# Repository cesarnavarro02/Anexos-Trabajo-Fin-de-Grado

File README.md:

# ANEXOS

## Anexo I: Códigos fuente
Este es el anexo de códigos. En él se encuentran todos los scripts realizados durante la elaboración del TFG. A continuación, se enumeran estos programas junto con una pequeña descripción:

- **GeneradorPerfilNACA.py**: Este programa genera un archivo ".stl" en el cual se encuentra el perfil NACA cuatro dígitos del código que ha sido introducido por el usuario.
- **ProgramaPlaca.py**: Este es el programa que gobierna el funcionamiento de la RaspberryPi.
- **GeneradorBlandAltman.py**: Este programa genera un gráfico Bland-Altman de las mediciones de presión.
- **GeneradorGraficasCp.py**: Este es el programa que elabora la gráfica de coeficientes de presión.

## Anexo II: Manuales y hojas de características
Este es el anexo de Manuales y Hojas de características. Como su propio nombre indica, en él se encuentran los manuales y hojas de características de componentes y sistemas que intervienen en el trabajo:

- **Datasheet SDP8xx-Digital**: Hoja de características del sensor de presión.
- **manual-anemometro-pce-hvac-2**: Manual del manómetro digital.
- **raspberry-pi-4-datasheet**: Hoja de características de la Raspberry Pi.

## Anexo III: Planos
En este Anexo se encuentra el plano del perfil acotado con sus cotas en milímetros. El documento tiene el nombre de `DibujoAla.pdf`.

## Anexo IV: Archivos para fabricación de placas
En este Anexo se encuentran los archivos del esquemático y del footprint de las placas junto con la librería con los componentes que se han diseñado. Para utilizar estos archivos es necesario tener instalado el software Eagle en su versión 7.5. Se debe crear un nuevo proyecto donde se importarán tanto el esquemático como el footprint de la placa que se desee fabricar. Además, se debe importar la librería que contiene el nombre `CESAR.lbr`, que contiene los componentes específicos de las placas.

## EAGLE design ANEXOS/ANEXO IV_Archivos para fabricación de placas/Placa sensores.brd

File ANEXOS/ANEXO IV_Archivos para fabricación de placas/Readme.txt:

En este Anexo se encuentran los archivos del esquemático y de el footprint de las placas junto con la librería con los
componentes que se han diseñado. Para utilizar estos archivos es necesario tener instalado el software Eagle en su 
versión 7.5. Se debe crear un nuevo proyecto donde se importarán tanto el esquemático como el footprint de la placa 
que se desee fabricar. Además se debe importar la librearía que contiene con nombre CESAR.lbr, que contiene los componentes
específicos de las placas.

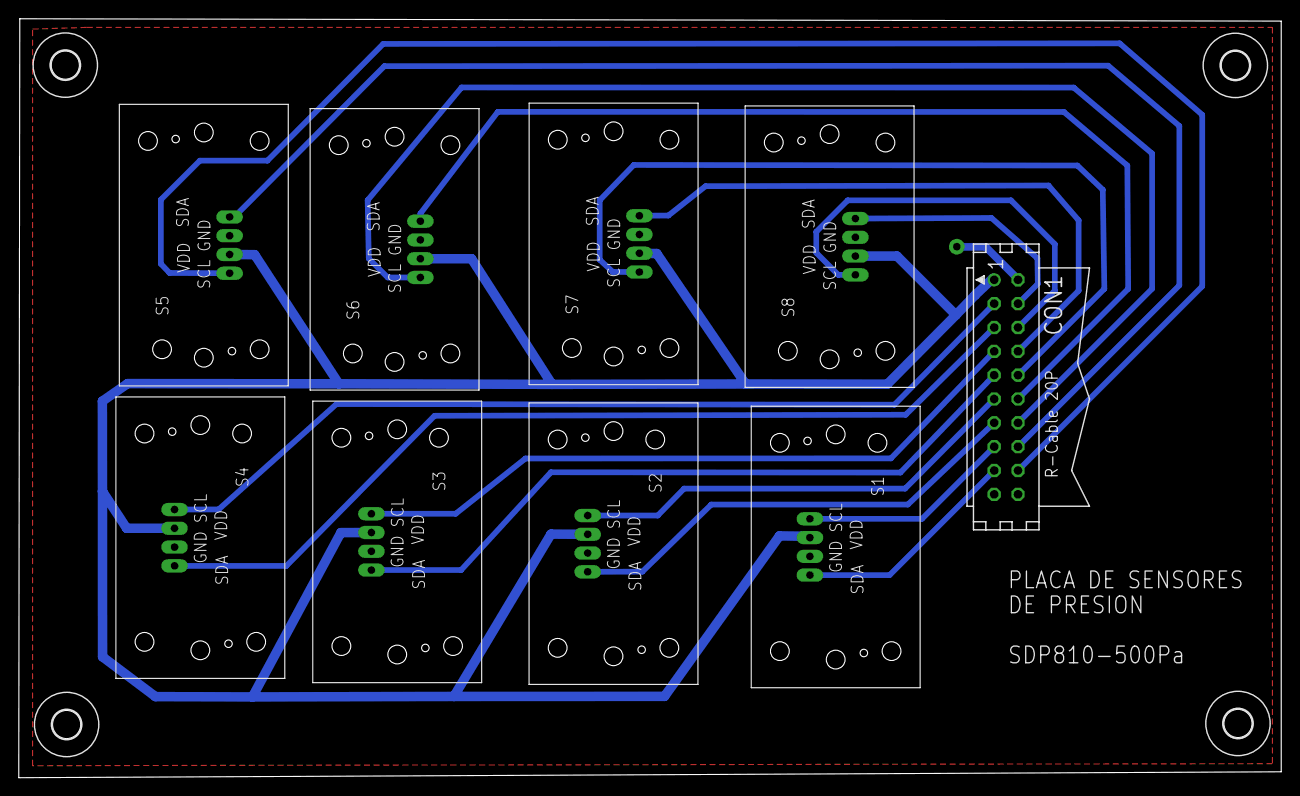
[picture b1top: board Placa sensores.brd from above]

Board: 2 copper layers, 134.5 x 80.9 mm, 13 parts (0 on the bottom side), 18 nets.

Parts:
CON1: CON20
H1, H2, H3, H4: MOUNT-HOLE3.0; 3,0
S1, S2, S3, S4, S5, S6, S7, S8: SDP810-500PA

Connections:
GND: CON1.2, S1.GND, S2.GND, S3.GND, S4.GND, S5.GND, S6.GND, S7.GND, S8.GND
unnamed: CON1.1, S1.VDD, S2.VDD, S3.VDD, S4.VDD, S5.VDD, S6.VDD, S7.VDD, S8.VDD
unnamed: CON1.6, S8.SCL
unnamed: CON1.8, S7.SDA
unnamed: CON1.10, S7.SCL
unnamed: CON1.18, S5.SCL
unnamed: CON1.16, S5.SDA
unnamed: CON1.14, S6.SCL
unnamed: CON1.4, S8.SDA
unnamed: CON1.12, S6.SDA
unnamed: CON1.3, S4.SCL
unnamed: CON1.5, S4.SDA
unnamed: CON1.7, S3.SCL
unnamed: CON1.9, S3.SDA
unnamed: CON1.17, S1.SDA
unnamed: CON1.15, S1.SCL
unnamed: CON1.11, S2.SCL
unnamed: CON1.13, S2.SDA

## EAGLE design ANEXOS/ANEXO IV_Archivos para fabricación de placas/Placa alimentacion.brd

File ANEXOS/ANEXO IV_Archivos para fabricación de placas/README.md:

En este Anexo se encuentran los archivos del esquemático y del footprint de las placas junto con la librería con los componentes que se han diseñado. Para utilizar estos archivos es necesario tener instalado el software **Eagle** en su versión 7.5. Se debe crear un nuevo proyecto donde se importarán tanto el esquemático como el footprint de la placa que se desee fabricar. Además, se debe importar la librería con el nombre **CESAR.lbr**, que contiene los componentes específicos de las placas.

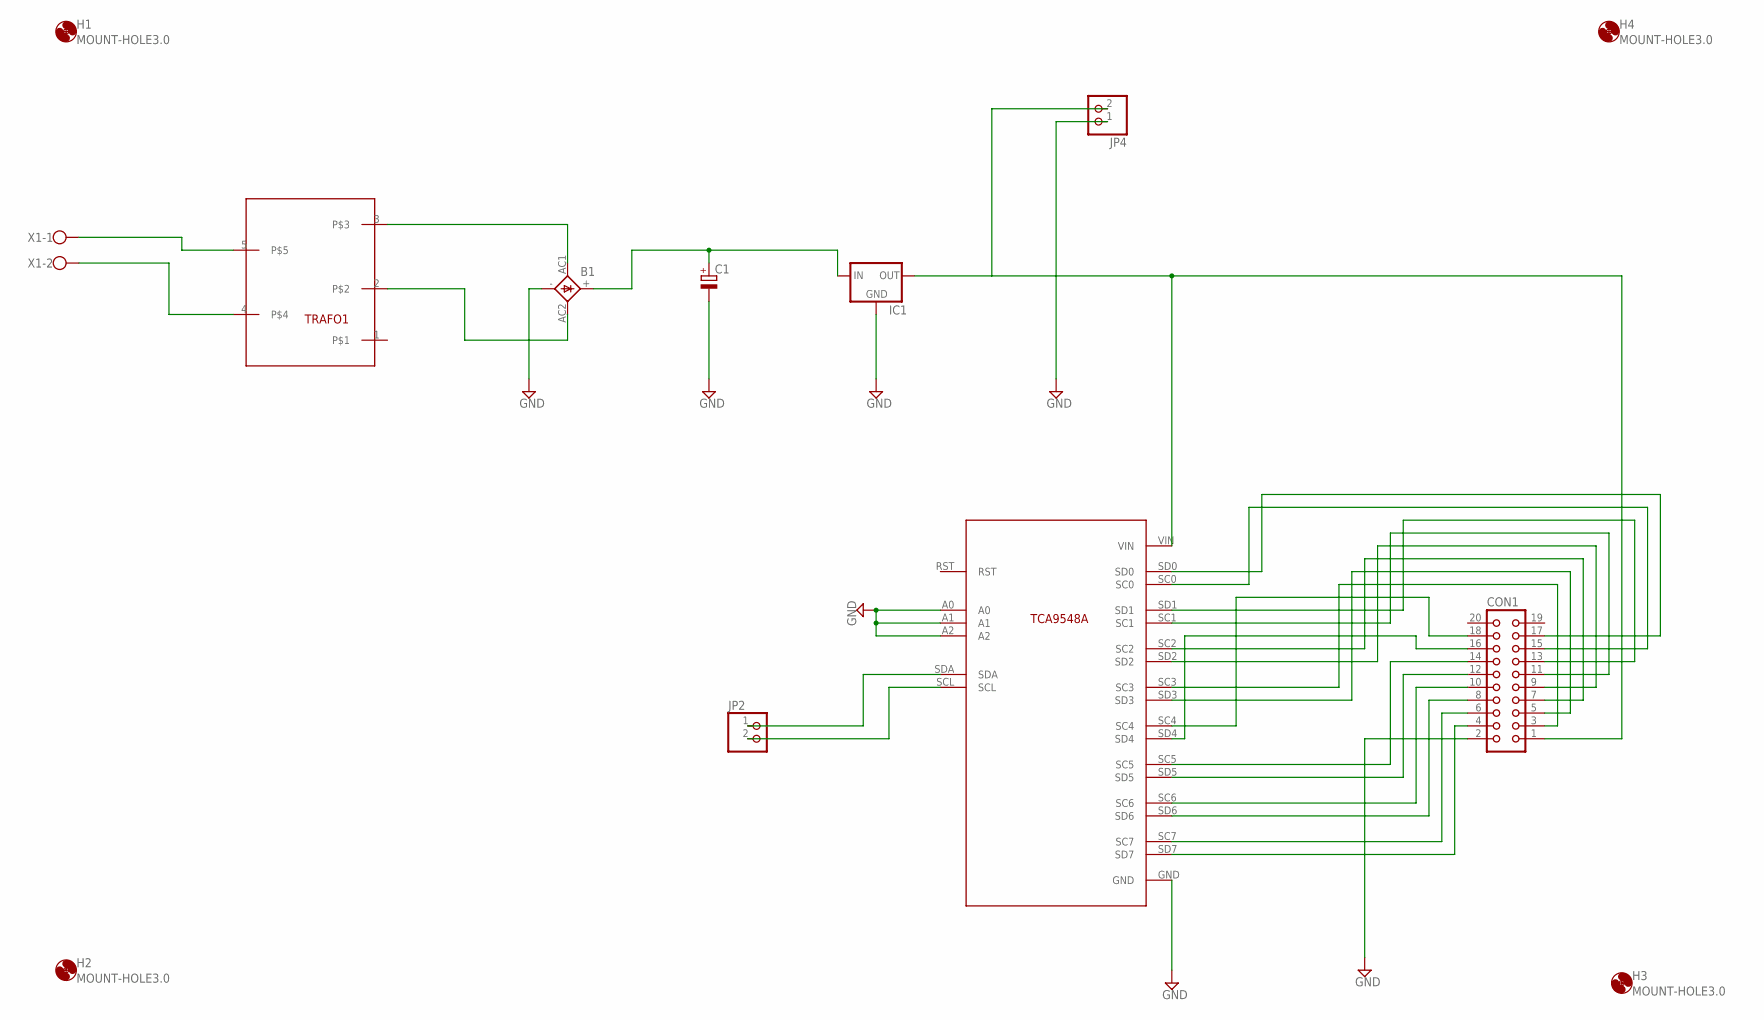
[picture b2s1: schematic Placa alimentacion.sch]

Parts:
B1: KBU
C1: CPOL-EUE5-8.5; E5-8,5
CON1: CON20
H1, H2, H3, H4: MOUNT-HOLE3.0; 3,0
IC1: 78MXXL
JP2, JP4: PINHD-1X2; 1X02
TRAFO1: ARISTON_TR5309
U$1: TCA9548A
X1: W237-102

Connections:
GND: B1.-, C1.-, CON1.2, IC1.GND, JP4.1, U$1.A0, U$1.A1, U$1.A2, U$1.GND
unnamed: TRAFO1.5, X1.1
unnamed: TRAFO1.4, X1.2
unnamed: B1.AC1, TRAFO1.3
unnamed: B1.AC2, TRAFO1.2
unnamed: B1.+, C1.+, IC1.IN
unnamed: CON1.3, U$1.SC3
unnamed: CON1.5, U$1.SD3
unnamed: CON1.7, U$1.SC2
unnamed: CON1.9, U$1.SD2
unnamed: CON1.11, U$1.SC1
unnamed: CON1.13, U$1.SD1
unnamed: CON1.15, U$1.SC0
unnamed: CON1.17, U$1.SD0
unnamed: CON1.4, U$1.SD7
unnamed: CON1.6, U$1.SC7
unnamed: CON1.8, U$1.SD6
unnamed: CON1.10, U$1.SC6
unnamed: CON1.12, U$1.SD5
unnamed: CON1.14, U$1.SC5
unnamed: CON1.16, U$1.SD4
unnamed: CON1.18, U$1.SC4
unnamed: CON1.1, IC1.OUT, JP4.2, U$1.VIN
unnamed: JP2.1, U$1.SDA
unnamed: JP2.2, U$1.SCL

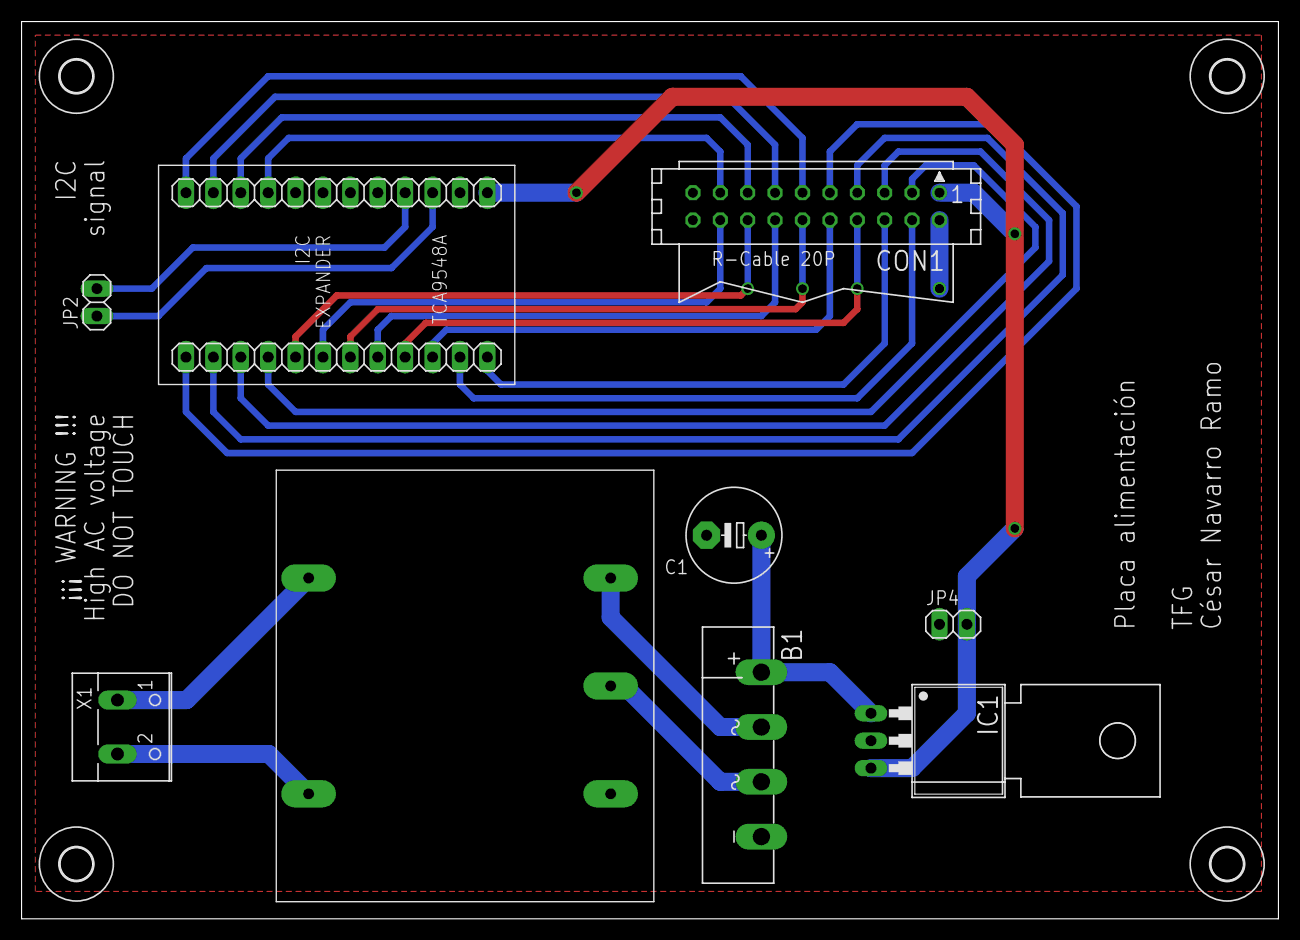
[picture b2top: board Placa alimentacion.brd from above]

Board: 2 copper layers, 116.5 x 83.2 mm, 13 parts (0 on the bottom side), 25 nets.
